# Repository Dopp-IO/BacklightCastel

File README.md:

Tiny castellated high-voltage backlight driver  
  
Part  Value     Package  
C1    4.7uF     C0603  
C2    1uF       C0603  
L1    22uH      IND_TAIYO_NRS5020  
R1    1.65M     R0603  
R2    71.5K     R0603  
U1    TLV61046A SOT-23-6  
  
Circuit outputs 19.2V @ 40mA in present configuration. Refer to TLV61046A datasheet to calculate values for other desired voltages.

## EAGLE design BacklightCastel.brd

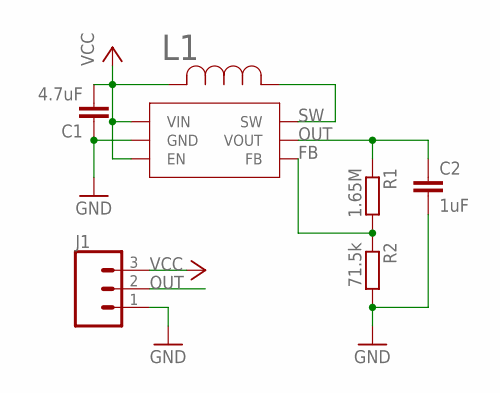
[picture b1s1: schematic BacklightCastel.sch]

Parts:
C1: 4.7uF; C0603
C2: 1uF; C0603
J1: CONN_03; 1X03
L1: 22uH; IND_TAIYO_NRS5020
R1: 1.65M; R0603
R2: 71.5k; R0603
U1: TLV61046A; SOT-23-6

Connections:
FB: R1.2, R2.1, U1.3 (FB)
GND: C1.1, C2.2, J1.1, R2.2, U1.2 (GND)
OUT: C2.1, J1.2, R1.1, U1.5 (VOUT)
SW: L1.1, U1.1 (SW)
VCC: C1.2, J1.3, L1.2, U1.4 (EN), U1.6 (VIN)

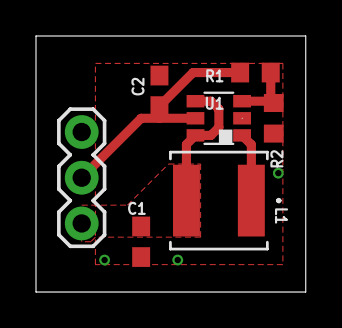
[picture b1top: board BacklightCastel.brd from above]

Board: 2 copper layers, 15.0 x 14.2 mm, 7 parts (0 on the bottom side), 5 nets.

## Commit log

2018-12-24 Formatted
2018-12-24 Added eagles, gerber & schematic in pdf
2019-01-20 Layout update
    Moved output capacitor, swapped R1 & R2, tied EN to VCC

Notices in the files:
parts and their libraries:
SparkFun-Connectors: Licensing: Creative Commons ShareAlike 4.0 International - https://creativecommons.org/licenses/by-sa/4.0
